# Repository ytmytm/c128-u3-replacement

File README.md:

# Advanced I/O space decoder for C128

This is a daughterboard that replaces U3 (74LS138) with a GAL22V10 as the I/O space address decoder providing extra features.

### C128DCR

### C128D

## Background

I needed it to split the I/O ($D000-$DFFF) space into more parts to support additional devices I had installed in my C128DCR: ACIA, SID#2 and CIA#3.

The daughterboard (bottom left, just above ROMs) mimics U3 that was already on the mainboard and generates additional chip select signals for:

- ACIA for [fast internal WiFi modem](https://github.com/dabonetn/Link232-Wifi) (top right)
- CIA#3 for [CIAIDE IDE interface for a harddisk drive](https://github.com/ytmytm/c64-ciaide) (top right, same daughterboard)
- SID#2 for dual/stereo SID chip tunes ([L-shaped daughterboard hugging dual MMU](https://github.com/ytmytm/c128-dcr-dual-sid) for [256K expansion](https://github.com/ytmytm/c128-mmu-256k-exp))

I wanted to have maximum compatibility with various Dual SID solutions and have the second SID available at least in $D420 and $D500 (in C64 mode) to cover majority of stereo/DualSID tunes.
It's available also optionally at $DE00, as if it was put on a cartridge.

I wanted the GAL to be socketed and the PCB to fit under the power supply.

### Second SID

Note that $D500 is decoded internally in PLA (U11) and the (unconnected) signal from U3 is never active on a stock C128, even in C64 mode. Without changing something
with U3 it's impossible to have second SID at $D500.

There is [another solution to that, focused only on the $D500 problem](https://github.com/hbekel/MixSID/tree/master/firmware/c128) in MixSID project. Simpler to install, but
it doesn't solve the issue of having second SID at $D420.

## Features

This solution provides some extra flexibility:

- SID#1 is active in $D400-$D41F and $D440-$D4FF areas always
- SID#2 signal is active in $D420-$D43F always, in $D500-$D51F in C64 mode and in $DE00-$DE1F if `SID2_DE00` jumper is shorted (in this case `I/O1` signal for $DE00-$DEFF activity *will not* be active on Expansion port)
- ACIA signal (meant for 6551 serial port) is active in $D700-$D7FF only if `ACIA_D700` jumper is shorted
- if `CIA3_DC20` jumper is shorted then CIA#1 is active in $DC00-$DC1F and $DC40-$DCFF areas
- if `CIA3_DC20` jumper is shorted then CIA#3 signal is active in $DC20-$DC3F
- if `CIA4_DD20` jumper is shorted then CIA#2 is active in $DD00-$DD1F and $DD40-$DDFF areas
- if `CIA4_DD20` jumper is shorted then CIA#4 signal is active in $DD20-$DD3F

## Design

### Idea

We want to mimic original behavior. Here is the part of C128DCR schematic with U3:

Whenever inputs G2/G3 are low (when I/O is accessed) we decode address lines A8/A9/A11 to generate chip select signals for pages $D4/$D5/$D6/$D7 and $DC/$DD/$DE/$DF.
This is routed to relevant chips: SID ($D4), VDC ($D6), CIA#1 ($DC), CIA#2 ($DD) and to the cartridge port pins I/O1 ($DE) and I/O2 ($DF).

Note that pins 14 ($D5) and 12 ($D7) are not connected. On a stock C128 you can connect one device to pin 12 to make it appear at $D700. The best choice is an internally installed ACIA (6551, SwiftLink)
because it's already supported by both C64 (ccgms) and C128 (DesTerm 128) excellent software.

### Schematic

There is not much to see on the [schematic](media/c128-u3-gal.pdf). The circuit is meant to replace the onboard U3 (74LS138) with a GAL22V10. Jumpers short certain signals to the ground
and enable additional functions.

[kicad](kicad/) folder contains all the KiCad 6.0 project files for C128DCR.

[kicad-c128d](kicad-c128d/) folder contains all the KiCad 6.0 project files for C128D. The schematic is identical, only PCB project differs.

### GAL

[gal-jed](gal-jed) folder contains GAL logic prepared in WinCUPL

- JED file to be flashed into GAL
- PLD, DOC files with logic equations
- SI file with simulation cases for complete testing

### Flashing GALs

Flash the [JED](gal-jed/C128-U3.jed) file into a GAL22V10. These devices are themselves obsolete. Chips that I had from an unknown Chinese source were clearly refurbished. ATMEL markings started to rub off even without using alcohol.

I have used TL866 II Plus to flash them. Remember to turn off "Encrypt chip" and "Lock bit" options.

### PCB

[kicad/plots](kicad/plots) folder contains Gerber files for manufacturing a **PCB that will fit C128DCR and not collide with the power supply**. It will **not** fit properly into C128D.

For a PCB that will fit in C128D look into [kicad-c128d/plots](kicad-c128d/plots)

## Installation

### Step 1

Start by removing U3 from the mainboard. Replace it with a socket. Put a 74LS138 back into the socket and check if everything works.

### Step 2

Prepare the PCB. Make sure to solder round pin headers into 74LS138 footprint. You can save square pin headers for jumpers. Install socket for GAL and put a flashed GAL22V10 there.

### Step 3

Remove 74LS138 from U3 socket and replace by the daughterboard. You can check if C128 starts. The keyboard (CIA#1) and disk drive (CIA#2) should work, but there will be no sound (check with CTRL+G in C128 mode).
This is because `A5` is not connected and so pulled high. This makes SID#1 inactive because all accesses are redirected to SID#2.

### Step 4

Connect two required signals:

- `A5` is available on CPU (U6) pin 12, on Z80 pin 35 and on U54 (74LS32) pin 12, but for me the closest place was to take it from any ROM, from pin 5
- `64/128` signal comes from PLA (U11) pin 15 or from MMU (U7) pin 47, but if you don't want to solder to chips it's also available on the mainboard as one of jumper J7 fields, just above U7

### Step 5

Setup jumpers - close (short to GND) to enable features, leave open to keep them disabled.

### Step 6

Connect output signals to your extra circuitry on C128DCR mainboard. In my case these were chip select signals for ACIA (SwiftLink at $D700), CIAIDE (CIA#3) and the second SID.

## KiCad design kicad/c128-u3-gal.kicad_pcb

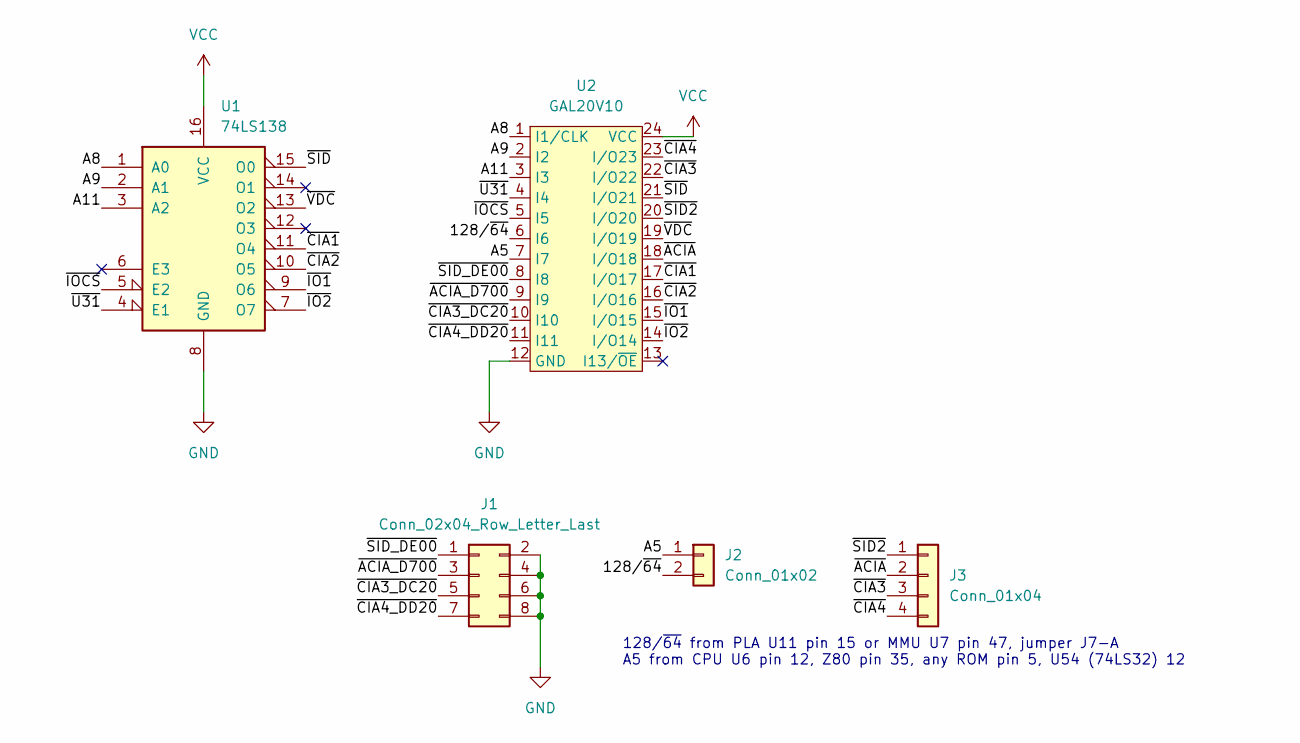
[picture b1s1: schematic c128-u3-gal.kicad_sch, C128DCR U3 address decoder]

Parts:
J1: Conn_02x04_Row_Letter_Last; PinHeader_2x04_P2.54mm_Vertical
J2: Conn_01x02; PinHeader_1x02_P2.54mm_Vertical
J3: Conn_01x04; PinHeader_1x04_P2.54mm_Vertical
U1: 74LS138; DIP-16_W7.62mm_LongPads
U2: GAL20V10; DIP-24_W7.62mm_LongPads

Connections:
/128/~64: J2.2, U2.6 (I6)
/A5: J2.1, U2.7 (I7)
/A8: U1.1 (A0), U2.1 (I1/CLK)
/A9: U1.2 (A1), U2.2 (I2)
/A11: U1.3 (A2), U2.3 (I3)
/~ACIA_D700: J1.3, U2.9 (I9)
/~ACIA: J3.2, U2.18 (I/O18)
/~CIA1: U1.11 (O4), U2.17 (I/O17)
/~CIA2: U1.10 (O5), U2.16 (I/O16)
/~CIA3_DC20: J1.5, U2.10 (I10)
/~CIA3: J3.3, U2.22 (I/O22)
/~CIA4_DD20: J1.7, U2.11 (I11)
/~CIA4: J3.4, U2.23 (I/O23)
/~IO1: U1.9 (O6), U2.15 (I/O15)
/~IO2: U1.7 (O7), U2.14 (I/O14)
/~IOCS: U1.5 (E2), U2.5 (I5)
/~SID2: J3.1, U2.20 (I/O20)
/~SID_DE00: J1.1, U2.8 (I8)
/~SID: U1.15 (O0), U2.21 (I/O21)
/~U31: U1.4 (E1), U2.4 (I4)
/~VDC: U1.13 (O2), U2.19 (I/O19)
GND: J1.2, J1.4, J1.6, J1.8, U1.8 (GND), U2.12 (GND)
VCC: U1.16 (VCC), U2.24 (VCC)

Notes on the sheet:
128/~{64} from PLA U11 pin 15 or MMU U7 pin 47, jumper J7-A A5 from CPU U6 pin 12, Z80 pin 35, any ROM pin 5, U54 (74LS32) 12

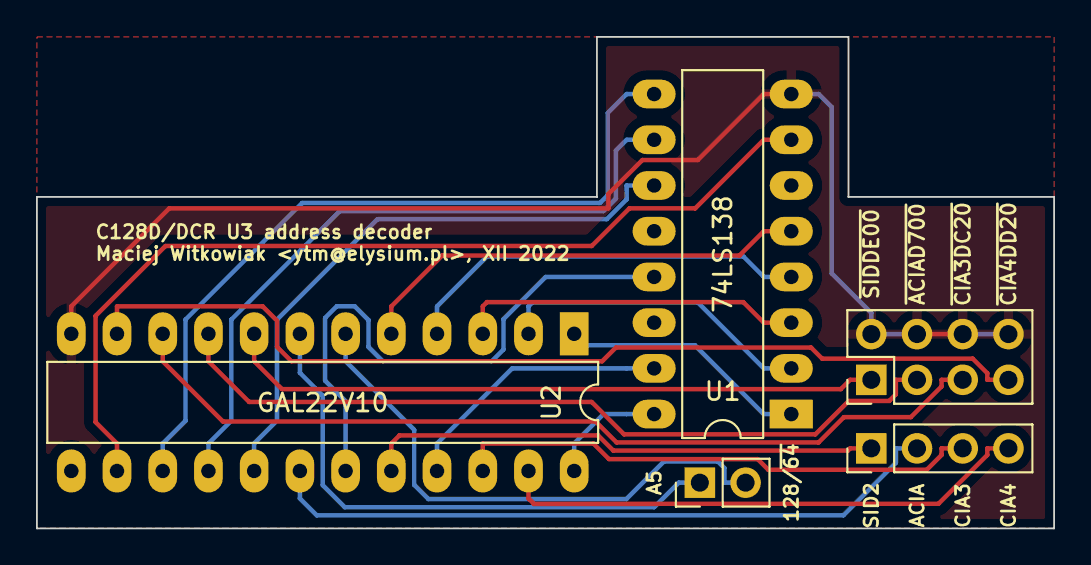
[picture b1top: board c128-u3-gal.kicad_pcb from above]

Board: 2 copper layers, 56.5 x 27.3 mm, 5 parts (0 on the bottom side), 23 nets.

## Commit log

2023-01-01 documentation
2023-01-01 more info
2023-01-03 pcb image
2023-01-05 dual SID board info
2023-10-24 PCB version that should fit in a C128D
2023-11-13 correct mistakes
2023-11-13 correct GAL device name to GAL22V10
2023-11-13 ignore temporary files
